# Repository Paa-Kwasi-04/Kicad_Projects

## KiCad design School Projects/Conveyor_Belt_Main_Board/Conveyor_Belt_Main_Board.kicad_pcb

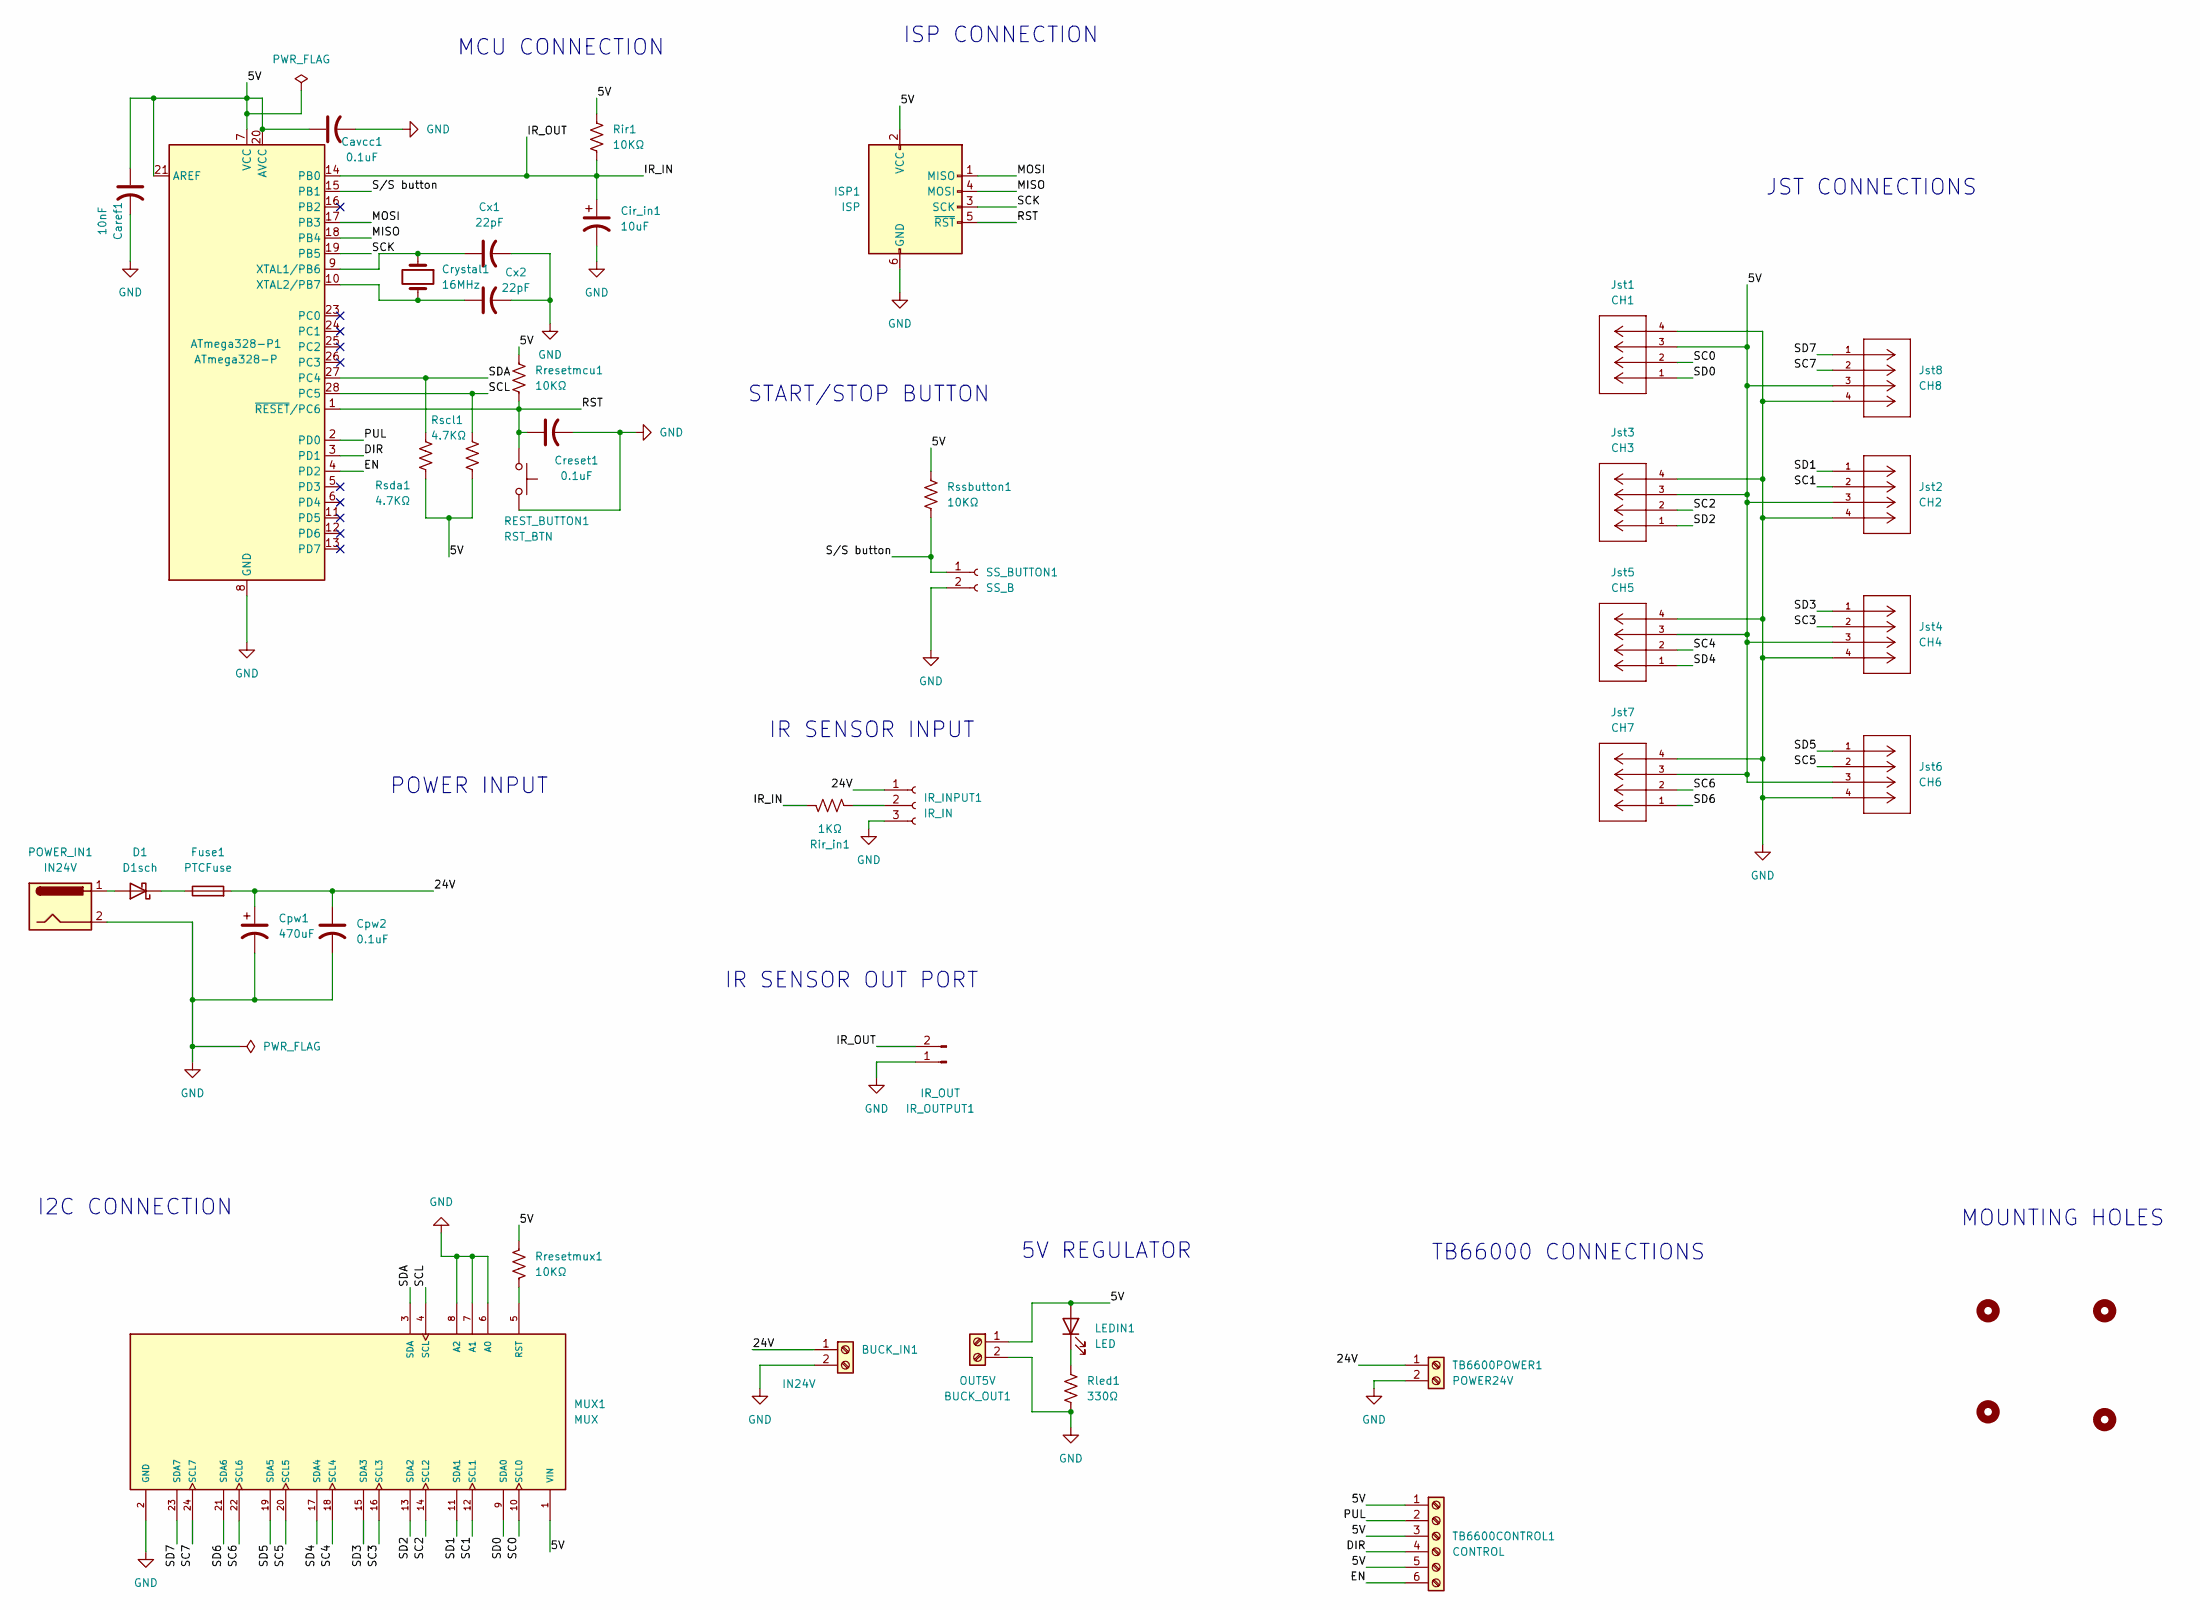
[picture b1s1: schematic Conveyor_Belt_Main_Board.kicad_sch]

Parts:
ATmega328-P1: ATmega328-P; DIP-28_W7.62mm
BUCK_IN1: IN24V; TerminalBlock_Phoenix_MKDS-1,5-2_1x02_P5.00mm_Horizontal
BUCK_OUT1: OUT5V; TerminalBlock_Phoenix_MKDS-1,5-2_1x02_P5.00mm_Horizontal
Caref1: 10nF; CP_Axial_L10.0mm_D4.5mm_P15.00mm_Horizontal
Cavcc1: 0.1uF; CP_Axial_L10.0mm_D4.5mm_P15.00mm_Horizontal
Cir_in1: 10uF; CP_Axial_L10.0mm_D4.5mm_P15.00mm_Horizontal
Cpw1: 470uF; CP_Axial_L10.0mm_D4.5mm_P15.00mm_Horizontal
Cpw2: 0.1uF; CP_Axial_L10.0mm_D4.5mm_P15.00mm_Horizontal
Creset1: 0.1uF; CP_Axial_L10.0mm_D4.5mm_P15.00mm_Horizontal
Crystal1: 16MHz; Crystal_HC49-4H_Vertical
Cx1, Cx2: 22pF; CP_Axial_L10.0mm_D4.5mm_P15.00mm_Horizontal
D1: D1sch; D_A-405_P12.70mm_Horizontal
Fuse1: PTCFuse; Fuse_Bourns_MF-RG400
H1, H2, H3, H4: MountingHole; MountingHole_2.7mm_Pad
IR_INPUT1: IR_IN; JST_EH_B3B-EH-A_1x03_P2.50mm_Vertical
IR_OUTPUT1: IR_OUT; JST_EH_B2B-EH-A_1x02_P2.50mm_Vertical
ISP1: ISP; PinHeader_1x06_P2.54mm_Vertical
Jst1: CH1; JST_PH_B4B-PH-K_1x04_P2.00mm_Vertical; MANUFACTURER_PART_NUMBER SM04B-SRSS-TB
Jst2: CH2; JST_PH_B4B-PH-K_1x04_P2.00mm_Vertical; MANUFACTURER_PART_NUMBER SM04B-SRSS-TB
Jst3: CH3; JST_PH_B4B-PH-K_1x04_P2.00mm_Vertical; MANUFACTURER_PART_NUMBER SM04B-SRSS-TB
Jst4: CH4; JST_PH_B4B-PH-K_1x04_P2.00mm_Vertical; MANUFACTURER_PART_NUMBER SM04B-SRSS-TB
Jst5: CH5; JST_PH_B4B-PH-K_1x04_P2.00mm_Vertical; MANUFACTURER_PART_NUMBER SM04B-SRSS-TB
Jst6: CH6; JST_PH_B4B-PH-K_1x04_P2.00mm_Vertical; MANUFACTURER_PART_NUMBER SM04B-SRSS-TB
Jst7: CH7; JST_PH_B4B-PH-K_1x04_P2.00mm_Vertical; MANUFACTURER_PART_NUMBER SM04B-SRSS-TB
Jst8: CH8; JST_PH_B4B-PH-K_1x04_P2.00mm_Vertical; MANUFACTURER_PART_NUMBER SM04B-SRSS-TB
LEDIN1: LED; LED_D3.0mm
MUX1: MUX; TCA954A_Multiplexer; PARTREV Sep 11, 2015
POWER_IN1: IN24V; TerminalBlock_Phoenix_MKDS-1,5-2_1x02_P5.00mm_Horizontal
REST_BUTTON1: RST_BTN; SW_PUSH_6mm
Rir1: 10KΩ; R_Axial_DIN0309_L9.0mm_D3.2mm_P12.70mm_Horizontal
Rir_in1: 1KΩ; R_Axial_DIN0309_L9.0mm_D3.2mm_P12.70mm_Horizontal
Rled1: 330Ω; R_Axial_DIN0309_L9.0mm_D3.2mm_P12.70mm_Horizontal
Rresetmcu1: 10KΩ; R_Axial_DIN0309_L9.0mm_D3.2mm_P12.70mm_Horizontal
Rresetmux1: 10KΩ; R_Axial_DIN0309_L9.0mm_D3.2mm_P12.70mm_Horizontal
Rscl1: 4.7KΩ; R_Axial_DIN0309_L9.0mm_D3.2mm_P12.70mm_Horizontal
Rsda1: 4.7KΩ; R_Axial_DIN0309_L9.0mm_D3.2mm_P12.70mm_Horizontal
Rssbutton1: 10KΩ; R_Axial_DIN0309_L9.0mm_D3.2mm_P12.70mm_Horizontal
SS_BUTTON1: SS_B; JST_EH_B2B-EH-A_1x02_P2.50mm_Vertical
TB6600CONTROL1: CONTROL; TerminalBlock_Phoenix_MKDS-1,5-6_1x06_P5.00mm_Horizontal
TB6600POWER1: POWER24V; TerminalBlock_Phoenix_MKDS-1,5-2_1x02_P5.00mm_Horizontal

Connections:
/5V: ATmega328-P1.7 (VCC), ATmega328-P1.20 (AVCC), ATmega328-P1.21 (AREF), BUCK_OUT1.1, Caref1.1, Cavcc1.1, ISP1.2 (VCC), Jst1.3, Jst2.3, Jst3.3, Jst4.3, Jst5.3, Jst6.3, Jst7.3, Jst8.3, LEDIN1.2 (A), MUX1.1 (VIN), Rir1.1, Rresetmcu1.1, Rresetmux1.1, Rscl1.2, Rsda1.2, Rssbutton1.1, TB6600CONTROL1.1, TB6600CONTROL1.3, TB6600CONTROL1.5
/24V: BUCK_IN1.1, Cpw1.1, Cpw2.1, Fuse1.2, IR_INPUT1.1, TB6600POWER1.1
/DIR: ATmega328-P1.3 (PD1), TB6600CONTROL1.4
/EN: ATmega328-P1.4 (PD2), TB6600CONTROL1.6
/IR_IN: ATmega328-P1.14 (PB0), Cir_in1.1, IR_OUTPUT1.2, Rir1.2, Rir_in1.1
/MISO: ATmega328-P1.18 (PB4), ISP1.4 (MOSI)
/MOSI: ATmega328-P1.17 (PB3), ISP1.1 (MISO)
/PUL: ATmega328-P1.2 (PD0), TB6600CONTROL1.2
/RST: ATmega328-P1.1 (~RESET/PC6), Creset1.1, ISP1.5 (~RST), REST_BUTTON1.1, Rresetmcu1.2
/SC0: Jst1.2, MUX1.10 (SCL0)
/SC1: Jst2.2, MUX1.12 (SCL1)
/SC2: Jst3.2, MUX1.14 (SCL2)
/SC3: Jst4.2, MUX1.16 (SCL3)
/SC4: Jst5.2, MUX1.18 (SCL4)
/SC5: Jst6.2, MUX1.20 (SCL5)
/SC6: Jst7.2, MUX1.22 (SCL6)
/SC7: Jst8.2, MUX1.24 (SCL7)
/SCK: ATmega328-P1.19 (PB5), ISP1.3 (SCK)
/SCL: ATmega328-P1.28 (PC5), MUX1.4 (SCL), Rscl1.1
/SD0: Jst1.1, MUX1.9 (SDA0)
/SD1: Jst2.1, MUX1.11 (SDA1)
/SD2: Jst3.1, MUX1.13 (SDA2)
/SD3: Jst4.1, MUX1.15 (SDA3)
/SD4: Jst5.1, MUX1.17 (SDA4)
/SD5: Jst6.1, MUX1.19 (SDA5)
/SD6: Jst7.1, MUX1.21 (SDA6)
/SD7: Jst8.1, MUX1.23 (SDA7)
/SDA: ATmega328-P1.27 (PC4), MUX1.3 (SDA), Rsda1.1
/S/S button: ATmega328-P1.15 (PB1), Rssbutton1.2, SS_BUTTON1.1
GND: ATmega328-P1.8 (GND), ATmega328-P1.22 (GND), BUCK_IN1.2, BUCK_OUT1.2, Caref1.2, Cavcc1.2, Cir_in1.2, Cpw1.2, Cpw2.2, Creset1.2, Cx1.2, Cx2.2, IR_INPUT1.3, IR_OUTPUT1.1, ISP1.6 (GND), Jst1.4, Jst2.4, Jst3.4, Jst4.4, Jst5.4, Jst6.4, Jst7.4, Jst8.4, MUX1.2 (GND), MUX1.6 (A0), MUX1.7 (A1), MUX1.8 (A2), POWER_IN1.2, REST_BUTTON1.2, Rled1.2, SS_BUTTON1.2, TB6600POWER1.2
unnamed: ATmega328-P1.9 (XTAL1/PB6), Crystal1.1, Cx1.1
unnamed: ATmega328-P1.10 (XTAL2/PB7), Crystal1.2, Cx2.1
unnamed: D1.2 (A), POWER_IN1.1
unnamed: D1.1 (K), Fuse1.1
unnamed: IR_INPUT1.2, Rir_in1.2
unnamed: LEDIN1.1 (K), Rled1.1
unnamed: MUX1.5 (RST), Rresetmux1.2

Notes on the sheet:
JST CONNECTIONS
ISP CONNECTION
MCU CONNECTION
5V REGULATOR
I2C CONNECTION
TB66000 CONNECTIONS
START/STOP BUTTON
MOUNTING HOLES
IR SENSOR INPUT
POWER INPUT
IR SENSOR OUT PORT

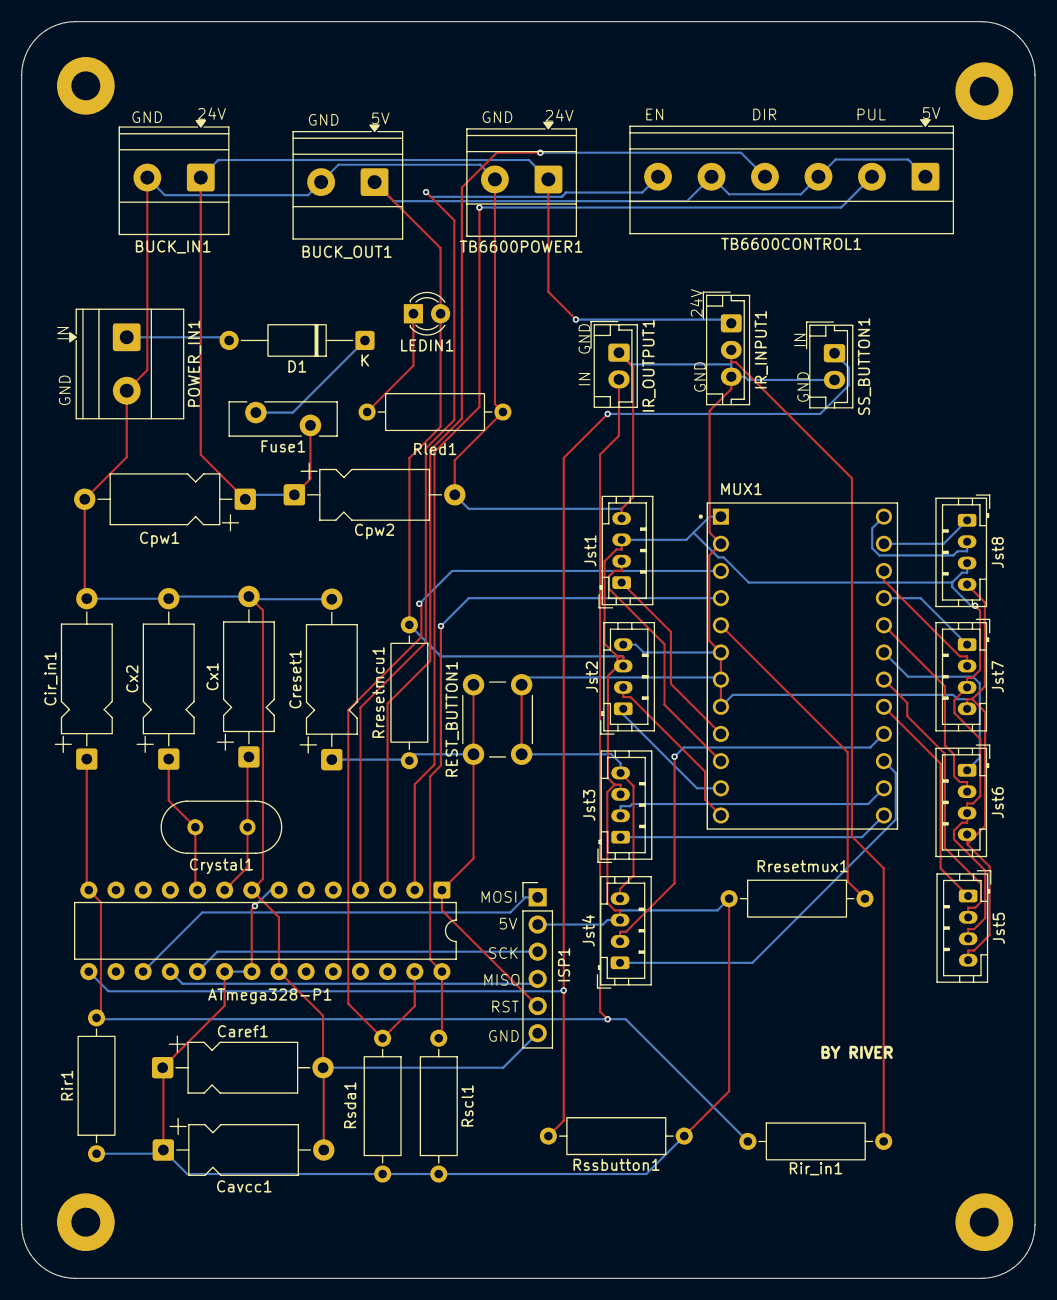
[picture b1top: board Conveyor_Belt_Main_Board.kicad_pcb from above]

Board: 2 copper layers, 94.8 x 117.5 mm, 44 parts (0 on the bottom side), 37 nets.

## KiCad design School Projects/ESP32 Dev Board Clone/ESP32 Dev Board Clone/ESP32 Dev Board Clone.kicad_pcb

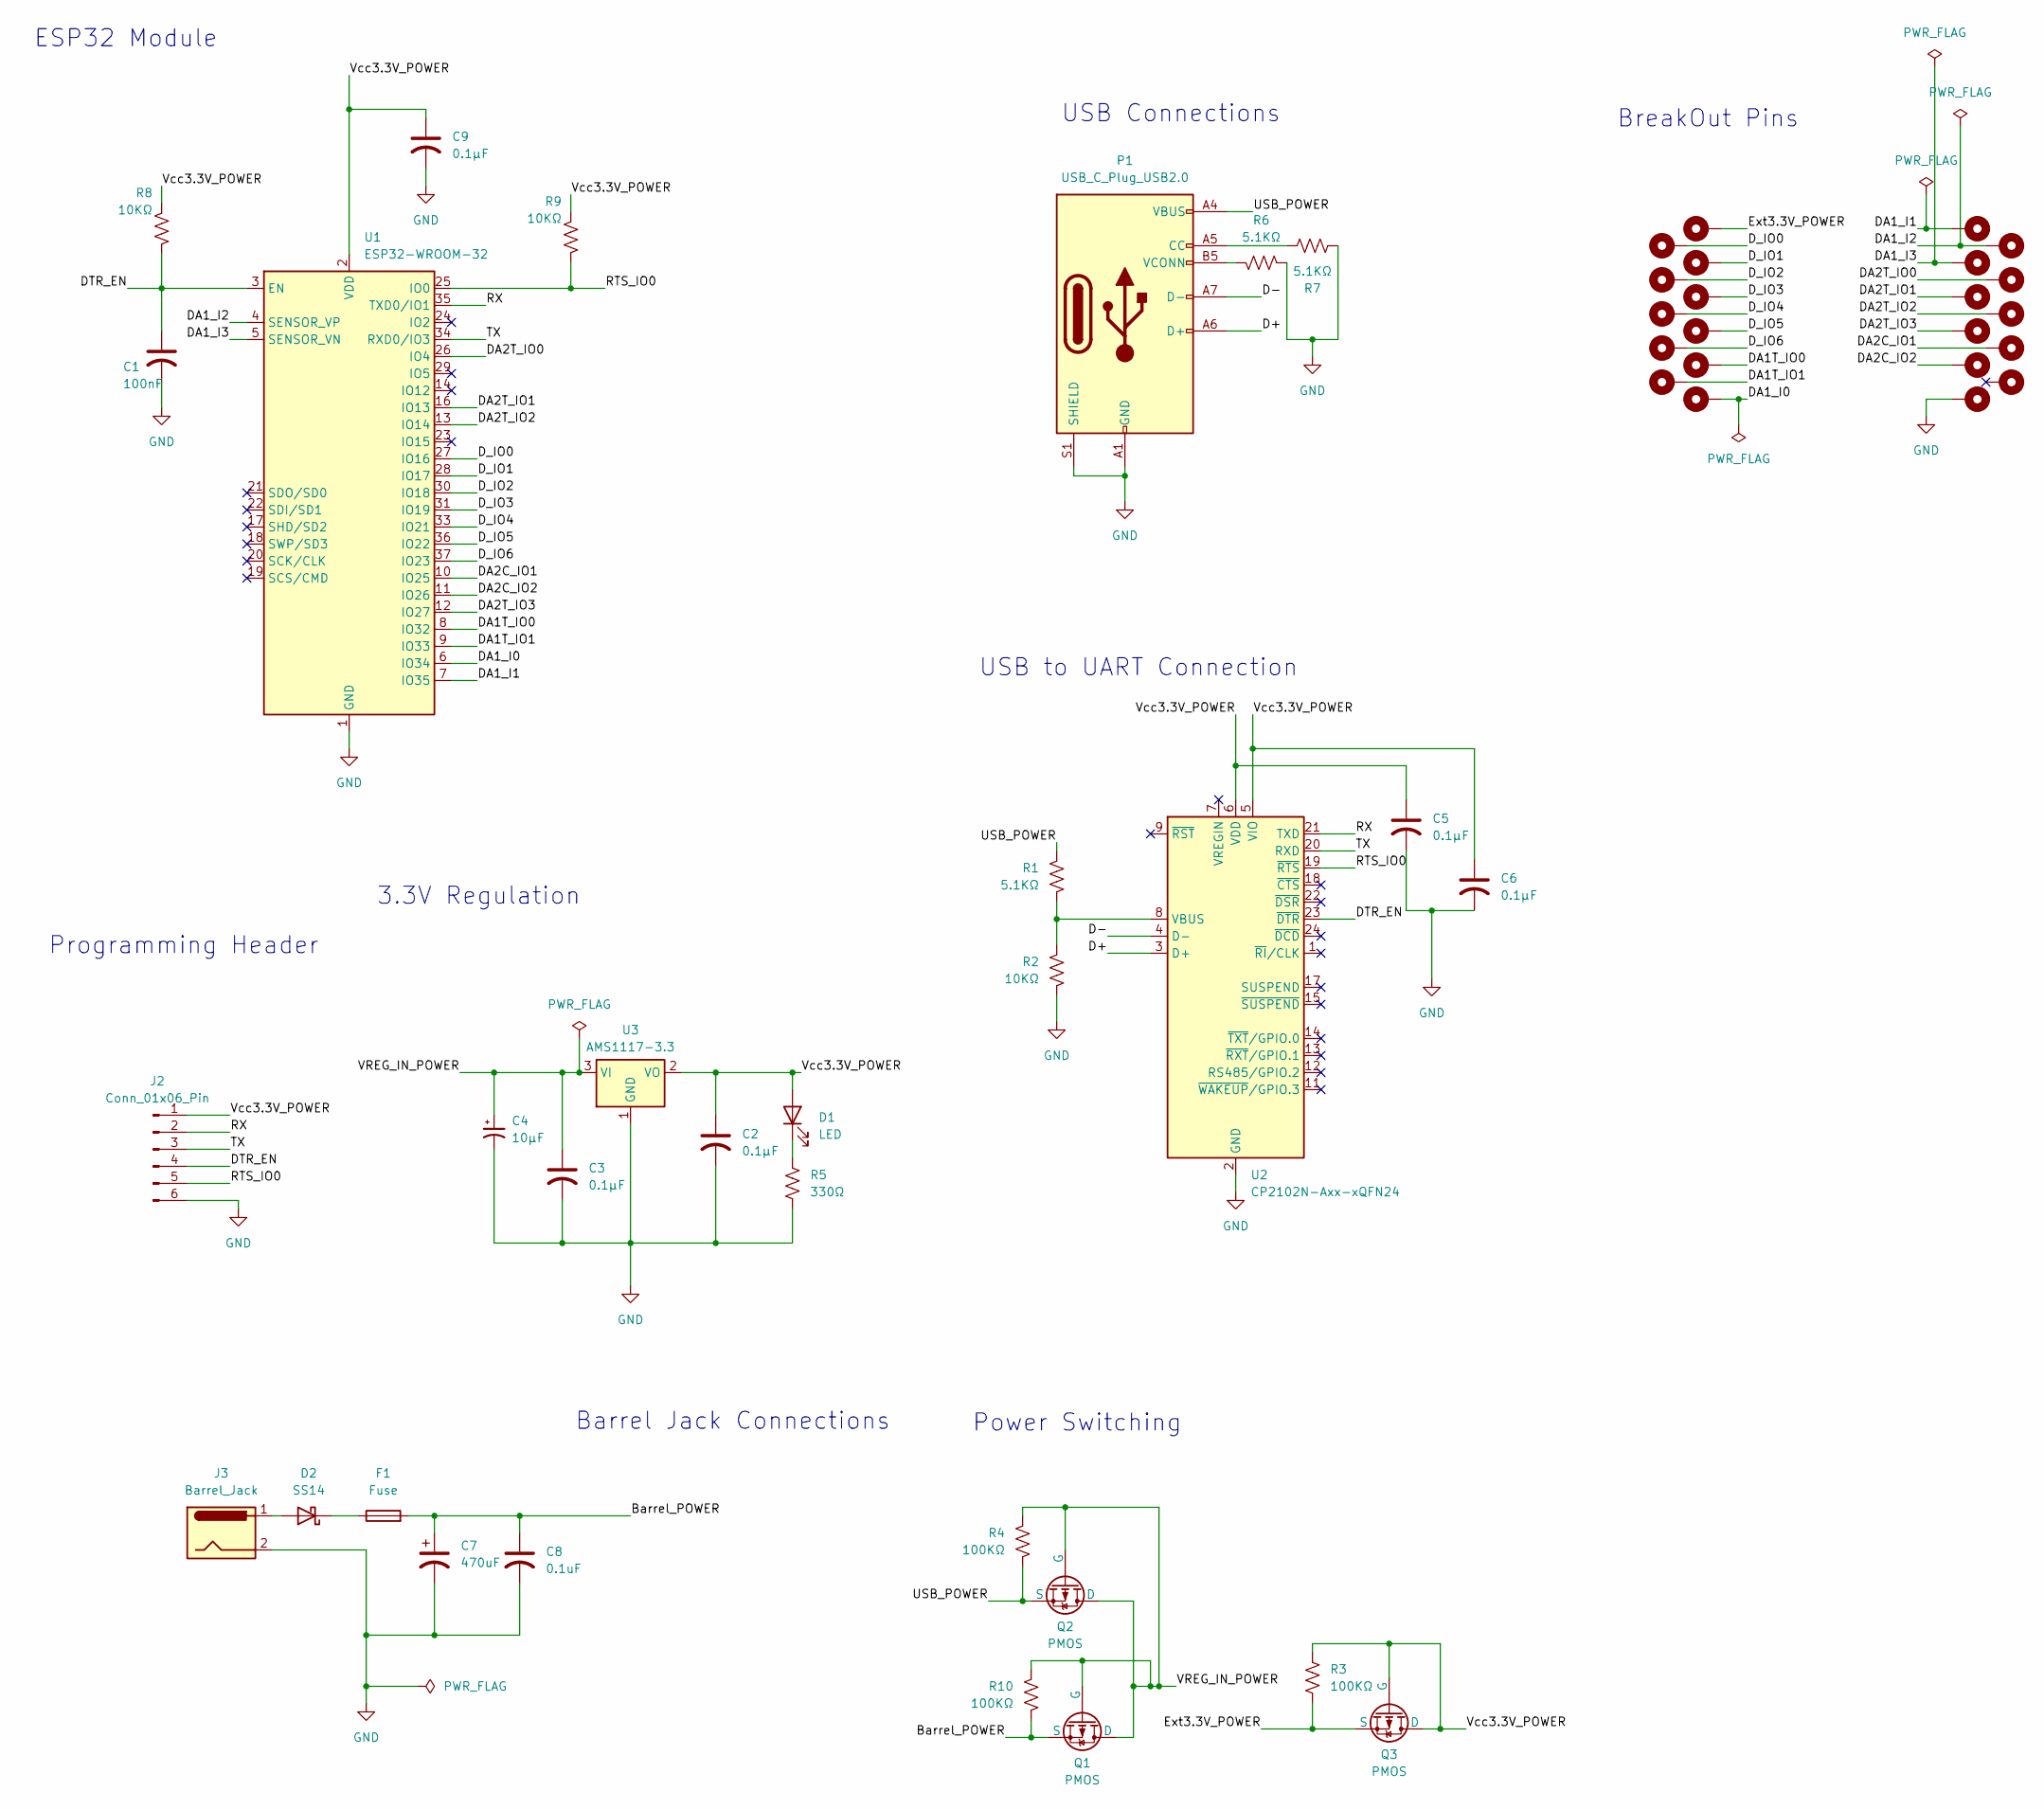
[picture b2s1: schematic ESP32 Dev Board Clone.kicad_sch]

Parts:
C1: 100nF; CP_EIA-1608-10_AVX-L
C2, C3, C5, C6, C9: 0.1µF; CP_EIA-1608-10_AVX-L
C4: 10µF; CP_EIA-1608-10_AVX-L
C7: 470uF; CP_EIA-1608-10_AVX-L
C8: 0.1uF; CP_EIA-1608-10_AVX-L
D1: LED; LED_0201_0603Metric
D2: SS14; D_0603_1608Metric_Pad1.05x0.95mm_HandSolder
F1: Fuse; Fuse_0603_1608Metric
H1: D_IO0; MountingHole_2.2mm_M2_DIN965_Pad_TopBottom
H2: Ext3.3V_POWER; MountingHole_2.2mm_M2_DIN965_Pad_TopBottom
H3: D_IO1; MountingHole_2.2mm_M2_DIN965_Pad_TopBottom
H4: D_IO2; MountingHole_2.2mm_M2_DIN965_Pad_TopBottom
H5: D_IO3; MountingHole_2.2mm_M2_DIN965_Pad_TopBottom
H6: D_IO4; MountingHole_2.2mm_M2_DIN965_Pad_TopBottom
H7: D_IO5; MountingHole_2.2mm_M2_DIN965_Pad_TopBottom
H8: D_IO6; MountingHole_2.2mm_M2_DIN965_Pad_TopBottom
H9: DA1T_IO0; MountingHole_2.2mm_M2_DIN965_Pad_TopBottom
H10: DA1T_IO1; MountingHole_2.2mm_M2_DIN965_Pad_TopBottom
H11: DA1_I0; MountingHole_2.2mm_M2_DIN965_Pad_TopBottom
H12: NC; MountingHole_2.2mm_M2_DIN965_Pad_TopBottom
H13: DA2C_IO1; MountingHole_2.2mm_M2_DIN965_Pad_TopBottom
H14: DA2T_IO2; MountingHole_2.2mm_M2_DIN965_Pad_TopBottom
H15: DA2T_IO0; MountingHole_2.2mm_M2_DIN965_Pad_TopBottom
H16: DA1_I2; MountingHole_2.2mm_M2_DIN965_Pad_TopBottom
H17: GND; MountingHole_2.2mm_M2_DIN965_Pad_TopBottom
H18: DA2C_IO2; MountingHole_2.2mm_M2_DIN965_Pad_TopBottom
H19: DA2T_IO3; MountingHole_2.2mm_M2_DIN965_Pad_TopBottom
H20: DA2T_IO1; MountingHole_2.2mm_M2_DIN965_Pad_TopBottom
H21: DA1_I3; MountingHole_2.2mm_M2_DIN965_Pad_TopBottom
H22: DA1_I1; MountingHole_2.2mm_M2_DIN965_Pad_TopBottom
J2: Conn_01x06_Pin; PinHeader_1x06_P2.54mm_Vertical
J3: Barrel_Jack; BarrelJack_GCT_DCJ200-10-A_Horizontal
P1: USB_C_Plug_USB2.0; USB_C_Receptacle_GCT_USB4085
Q1, Q2, Q3: PMOS; SuperSOT-3
R1, R6, R7: 5.1KΩ; R_0201_0603Metric
R2, R8, R9: 10KΩ; R_0201_0603Metric
R3, R4, R10: 100KΩ; R_0201_0603Metric
R5: 330Ω; R_0201_0603Metric
U1: ESP32-WROOM-32
U2: CP2102N-Axx-xQFN24; QFN-24-1EP_4x4mm_P0.5mm_EP2.6x2.6mm
U3: AMS1117-3.3; SOT-223-3_TabPin2

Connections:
/Barrel_POWER: C7.1, C8.1, F1.2, Q1.3 (S), R10.2
/D+: P1.A6 (D+), U2.3 (D+)
/D-: P1.A7 (D-), U2.4 (D-)
/DA1T_IO0: H9.1, U1.8 (IO32)
/DA1T_IO1: H10.1, U1.9 (IO33)
/DA1_I0: H11.1, U1.6 (IO34)
/DA1_I1: H22.1, U1.7 (IO35)
/DA1_I2: H16.1, U1.4 (SENSOR_VP)
/DA1_I3: H21.1, U1.5 (SENSOR_VN)
/DA2C_IO1: H13.1, U1.10 (IO25)
/DA2C_IO2: H18.1, U1.11 (IO26)
/DA2T_IO0: H15.1, U1.26 (IO4)
/DA2T_IO1: H20.1, U1.16 (IO13)
/DA2T_IO2: H14.1, U1.13 (IO14)
/DA2T_IO3: H19.1, U1.12 (IO27)
/DTR_EN: C1.1, J2.4, R8.2, U1.3 (EN), U2.23 (~DTR)
/D_IO0: H1.1, U1.27 (IO16)
/D_IO1: H3.1, U1.28 (IO17)
/D_IO2: H4.1, U1.30 (IO18)
/D_IO3: H5.1, U1.31 (IO19)
/D_IO4: H6.1, U1.33 (IO21)
/D_IO5: H7.1, U1.36 (IO22)
/D_IO6: H8.1, U1.37 (IO23)
/Ext3.3V_POWER: H2.1, Q3.3 (S), R3.2
/RTS_IO0: J2.5, R9.2, U1.25 (IO0), U2.19 (~RTS)
/RX: J2.2, U1.35 (TXD0/IO1), U2.21 (TXD)
/TX: J2.3, U1.34 (RXD0/IO3), U2.20 (RXD)
/USB_POWER: P1.A4 (VBUS), P1.A9 (VBUS), P1.B4 (VBUS), P1.B9 (VBUS), Q2.3 (S), R1.2, R4.2
/VREG_IN_POWER: C3.1, C4.1, Q1.1 (D), Q1.2 (G), Q2.1 (D), Q2.2 (G), R4.1, R10.1, U3.3 (VI)
/Vcc3.3V_POWER: C2.1, C5.1, C6.1, C9.1, D1.2 (A), J2.1, Q3.1 (D), Q3.2 (G), R3.1, R8.1, R9.1, U1.2 (VDD), U2.5 (VIO), U2.6 (VDD), U3.2 (VO)
GND: C1.2, C2.2, C3.2, C4.2, C5.2, C6.2, C7.2, C8.2, C9.2, H17.1, J2.6, J3.2, P1.A1 (GND), P1.A12 (GND), P1.B1 (GND), P1.B12 (GND), P1.S1 (SHIELD), R2.1, R5.2, R6.2, R7.2, U1.1 (GND), U1.15 (GND), U1.38 (GND), U1.39 (GND), U2.2 (GND), U2.25 (GND), U3.1 (GND)
unnamed: D1.1 (K), R5.1
unnamed: D2.2 (A), J3.1
unnamed: D2.1 (K), F1.1
unnamed: P1.A5 (CC), R7.1
unnamed: P1.B5 (VCONN), R6.1
unnamed: R1.1, R2.2, U2.8 (VBUS)

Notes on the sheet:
Barrel Jack Connections
USB to UART Connection
BreakOut Pins
ESP32 Module
Programming Header
USB Connections
3.3V Regulation
Power Switching

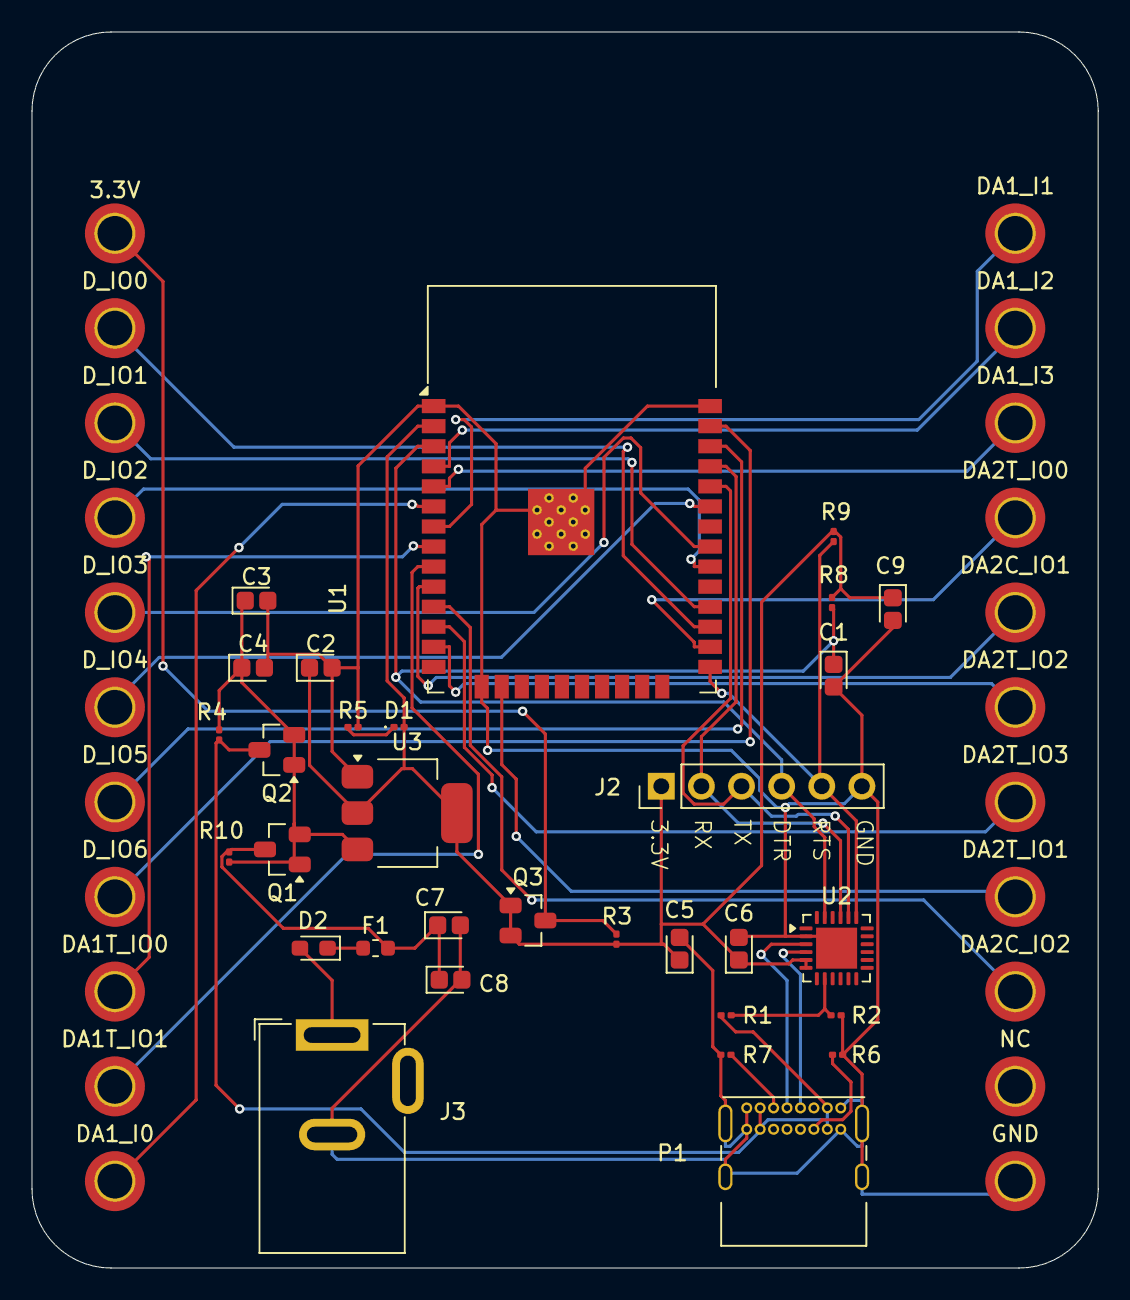
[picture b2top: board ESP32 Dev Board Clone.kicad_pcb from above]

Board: 2 copper layers, 67.5 x 78.2 mm, 53 parts (0 on the bottom side), 37 nets.

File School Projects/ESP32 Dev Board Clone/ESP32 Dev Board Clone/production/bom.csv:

Designator,Footprint,Quantity,Value,LCSC Part #
C1,CP_EIA-1608-10_AVX-L,1,100nF,
"C2, C3, C5, C6, C9",CP_EIA-1608-10_AVX-L,5,0.1µF,
C4,CP_EIA-1608-10_AVX-L,1,10µF,
C7,CP_EIA-1608-10_AVX-L,1,470uF,
C8,CP_EIA-1608-10_AVX-L,1,0.1uF,
D1,0201,1,LED,
D2,0603,1,SS14,
F1,0603,1,Fuse,
J2,PinHeader_1x06_P2.54mm_Vertical,1,Conn_01x06_Pin,
J3,BarrelJack_GCT_DCJ200-10-A_Horizontal,1,Barrel_Jack,
P1,USB_C_Receptacle_GCT_USB4085,1,USB_C_Plug_USB2.0,
"Q1, Q2, Q3",SuperSOT-3,3,PMOS,
"R1, R6, R7",0201,3,5.1KΩ,
"R10, R3, R4",0201,3,100KΩ,
"R2, R8, R9",0201,3,10KΩ,
R5,0201,1,330Ω,
U1,ESP32-WROOM-32,1,ESP32-WROOM-32,
U2,QFN-24-1EP_4x4mm_P0.5mm_EP2.6x2.6mm,1,CP2102N-Axx-xQFN24,
U3,SOT-223-3_TabPin2,1,AMS1117-3.3,

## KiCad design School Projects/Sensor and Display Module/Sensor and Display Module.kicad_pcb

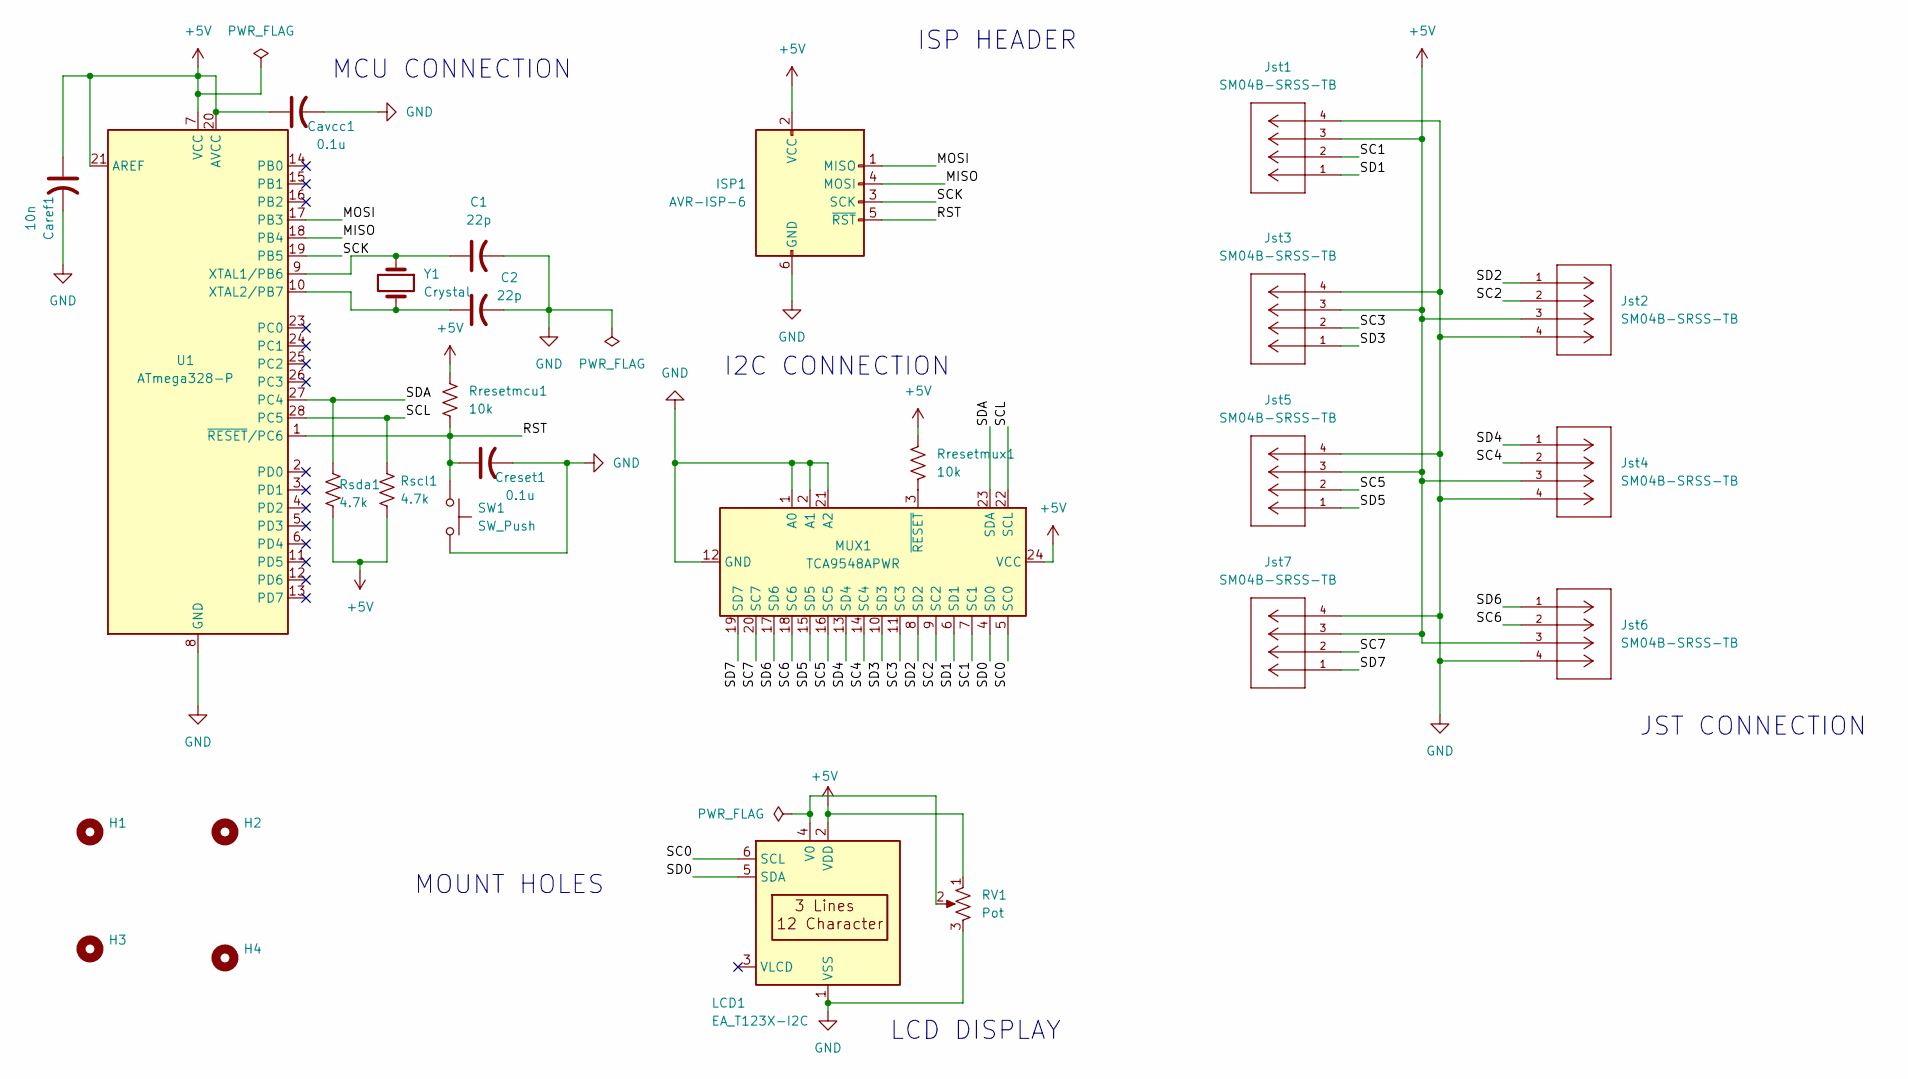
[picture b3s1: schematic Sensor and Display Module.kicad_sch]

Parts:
C1, C2: 22p; C_0805_2012Metric
Caref1: 10n; C_0805_2012Metric
Cavcc1: 0.1u; C_0805_2012Metric
Creset1: 0.1u; C_0805_2012Metric
H1, H2, H3, H4: MountingHole; MountingHole_2.7mm_Pad
ISP1: AVR-ISP-6; PinHeader_1x06_P2.54mm_Vertical
Jst1, Jst2, Jst3, Jst4, Jst5, Jst6, Jst7: SM04B-SRSS-TB; JST_GH_BM04B-GHS-TBT_1x04-1MP_P1.25mm_Vertical; MANUFACTURER_PART_NUMBER SM04B-SRSS-TB
LCD1: EA_T123X-I2C
MUX1: TCA9548APWR; TSSOP-24_4.4x7.8mm_P0.65mm
RV1: Pot; Potentiometer_Bourns_3314J_Vertical
Rresetmcu1: 10k; R_0805_2012Metric_Pad1.20x1.40mm_HandSolder
Rresetmux1: 10k; R_0805_2012Metric_Pad1.20x1.40mm_HandSolder
Rscl1: 4.7k; R_0805_2012Metric_Pad1.20x1.40mm_HandSolder
Rsda1: 4.7k; R_0805_2012Metric_Pad1.20x1.40mm_HandSolder
SW1: SW_Push; SW_PUSH_6mm
U1: ATmega328-P; DIP-28_W7.62mm
Y1: Crystal; Crystal_HC49-4H_Vertical

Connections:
+5V: Caref1.1, Cavcc1.1, ISP1.2 (VCC), Jst1.3, Jst2.3, Jst3.3, Jst4.3, Jst5.3, Jst6.3, Jst7.3, LCD1.2 (VDD), MUX1.24 (VCC), RV1.1, Rresetmcu1.1, Rresetmux1.1, Rscl1.2, Rsda1.2, U1.7 (VCC), U1.20 (AVCC), U1.21 (AREF)
/MISO: ISP1.4 (MOSI), U1.18 (PB4)
/MOSI: ISP1.1 (MISO), U1.17 (PB3)
/RST: Creset1.1, ISP1.5 (~RST), Rresetmcu1.2, SW1.1, U1.1 (~RESET/PC6); also elsewhere on the board
/SC0: LCD1.6 (SCL), MUX1.5 (SC0)
/SC1: Jst1.2, MUX1.7 (SC1)
/SC2: Jst2.2, MUX1.9 (SC2)
/SC3: Jst3.2, MUX1.11 (SC3)
/SC4: Jst4.2, MUX1.14 (SC4)
/SC5: Jst5.2, MUX1.16 (SC5)
/SC6: Jst6.2, MUX1.18 (SC6)
/SC7: Jst7.2, MUX1.20 (SC7)
/SCK: ISP1.3 (SCK), U1.19 (PB5)
/SCL: MUX1.22 (SCL), Rscl1.1, U1.28 (PC5)
/SD0: LCD1.5 (SDA), MUX1.4 (SD0)
/SD1: Jst1.1, MUX1.6 (SD1)
/SD2: Jst2.1, MUX1.8 (SD2)
/SD3: Jst3.1, MUX1.10 (SD3)
/SD4: Jst4.1, MUX1.13 (SD4)
/SD5: Jst5.1, MUX1.15 (SD5)
/SD6: Jst6.1, MUX1.17 (SD6)
/SD7: Jst7.1, MUX1.19 (SD7)
/SDA: MUX1.23 (SDA), Rsda1.1, U1.27 (PC4)
GND: C1.2, C2.2, Caref1.2, Cavcc1.2, Creset1.2, ISP1.6 (GND), Jst1.4, Jst2.4, Jst3.4, Jst4.4, Jst5.4, Jst6.4, Jst7.4, LCD1.1 (VSS), MUX1.1 (A0), MUX1.2 (A1), MUX1.12 (GND), MUX1.21 (A2), RV1.3, SW1.2, U1.8 (GND), U1.22 (GND); also elsewhere on the board
unnamed: LCD1.4 (V0), RV1.2
unnamed: MUX1.3 (~RESET), Rresetmux1.2
unnamed 26: C1.1, U1.9 (XTAL1/PB6), Y1.1; also elsewhere on the board
unnamed 27: C2.1, U1.10 (XTAL2/PB7), Y1.2; also elsewhere on the board

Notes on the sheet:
MCU CONNECTION
LCD DISPLAY
I2C CONNECTION
ISP HEADER
MOUNT HOLES
JST CONNECTION

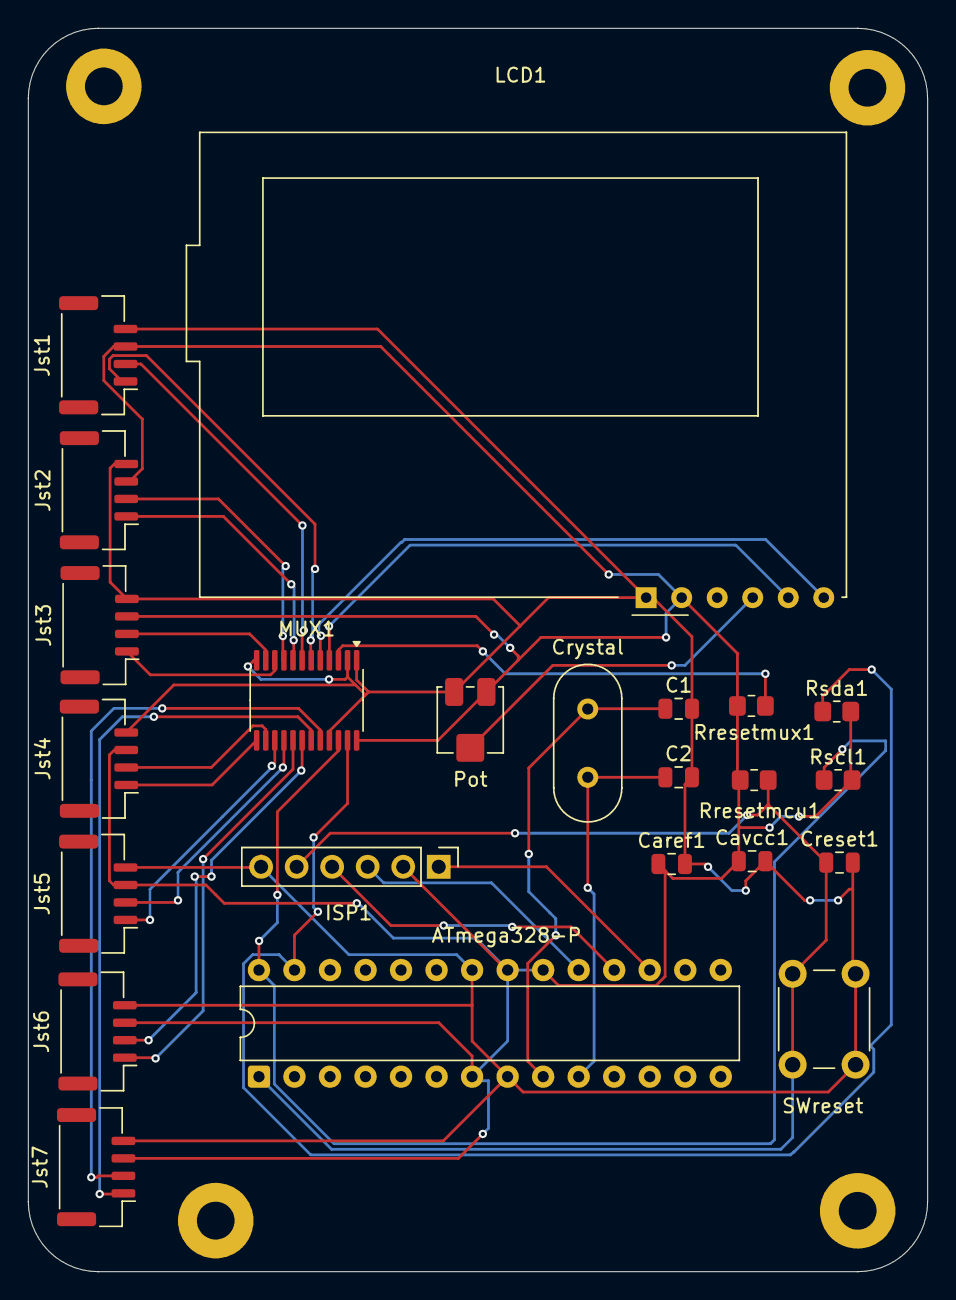
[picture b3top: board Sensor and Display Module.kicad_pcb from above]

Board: 2 copper layers, 64.3 x 88.9 mm, 27 parts (0 on the bottom side), 28 nets.

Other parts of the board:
Crystal: Y1; Crystal_HC49-4H_Vertical
SWreset: SW_Push; SW_PUSH_6mm

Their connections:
/RST: SWreset.1; also elsewhere on the board
GND: SWreset.2; also elsewhere on the board
unnamed 26: Crystal.1; also elsewhere on the board
unnamed 27: Crystal.2; also elsewhere on the board

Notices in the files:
parts and their libraries:
COPYRIGHT: Copyright (C) 2024 Ultra Librarian. All rights reserved.
